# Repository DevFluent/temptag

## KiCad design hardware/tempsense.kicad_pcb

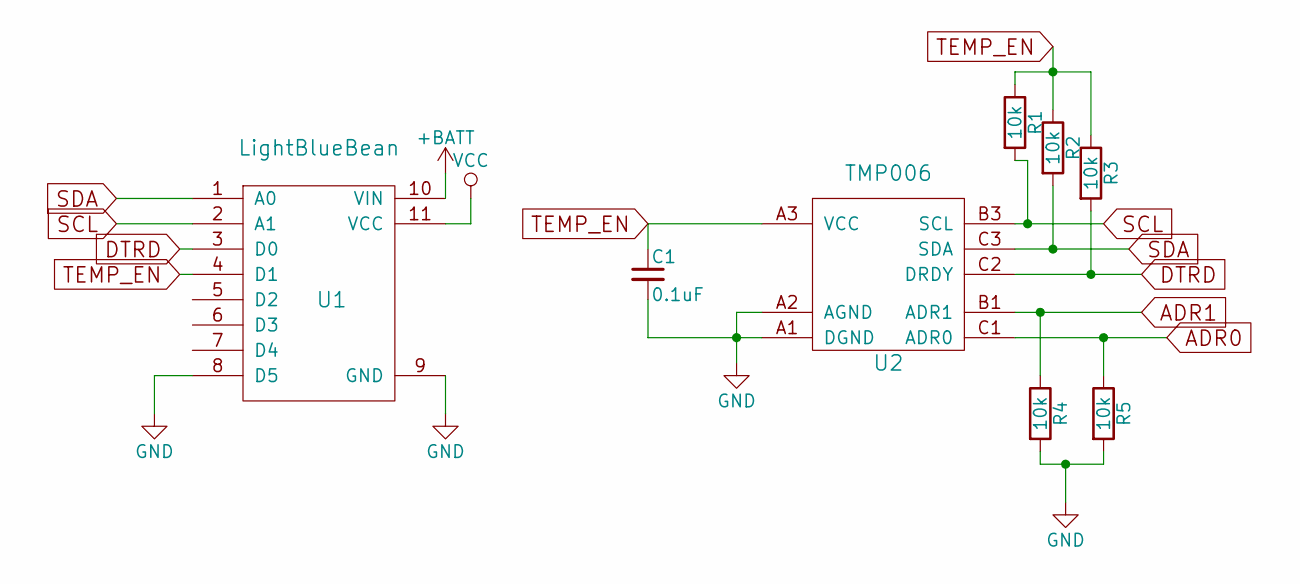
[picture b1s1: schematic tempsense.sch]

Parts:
C1: 0.1uF; C_0402_Hand; Digikey Part No. 490-6328-1-ND
R1, R2, R3, R4, R5: 10k; R_0402_Hand; Digikey Part No. 311-10KJRCT-ND
U1: LightBlueBean
U2: TMP006

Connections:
+BATT: U1.10 (VIN)
ADR0: R5.1, U2.C1 (ADR0)
ADR1: R4.1, U2.B1 (ADR1)
DTRD: R3.2, U1.3 (D0), U2.C2 (DRDY)
GND: C1.2, R4.2, R5.2, U1.8 (D5), U1.9 (GND), U2.A1 (DGND), U2.A2 (AGND)
SCL: R1.2, U1.2 (A1), U2.B3 (SCL)
SDA: R2.2, U1.1 (A0), U2.C3 (SDA)
TEMP_EN: C1.1, R1.1, R2.1, R3.1, U1.4 (D1), U2.A3 (VCC)
VCC: U1.11 (VCC)

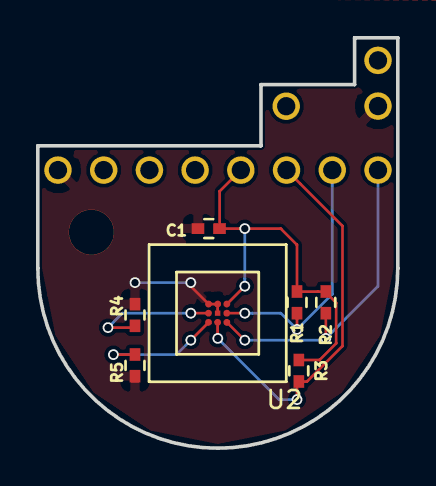
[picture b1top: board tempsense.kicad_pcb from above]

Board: 2 copper layers, 20.0 x 22.8 mm, 8 parts (1 on the bottom side), 7 nets.
